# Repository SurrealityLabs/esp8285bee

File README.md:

# esp8285bee
ESP8285 board in an XBee-compatible format

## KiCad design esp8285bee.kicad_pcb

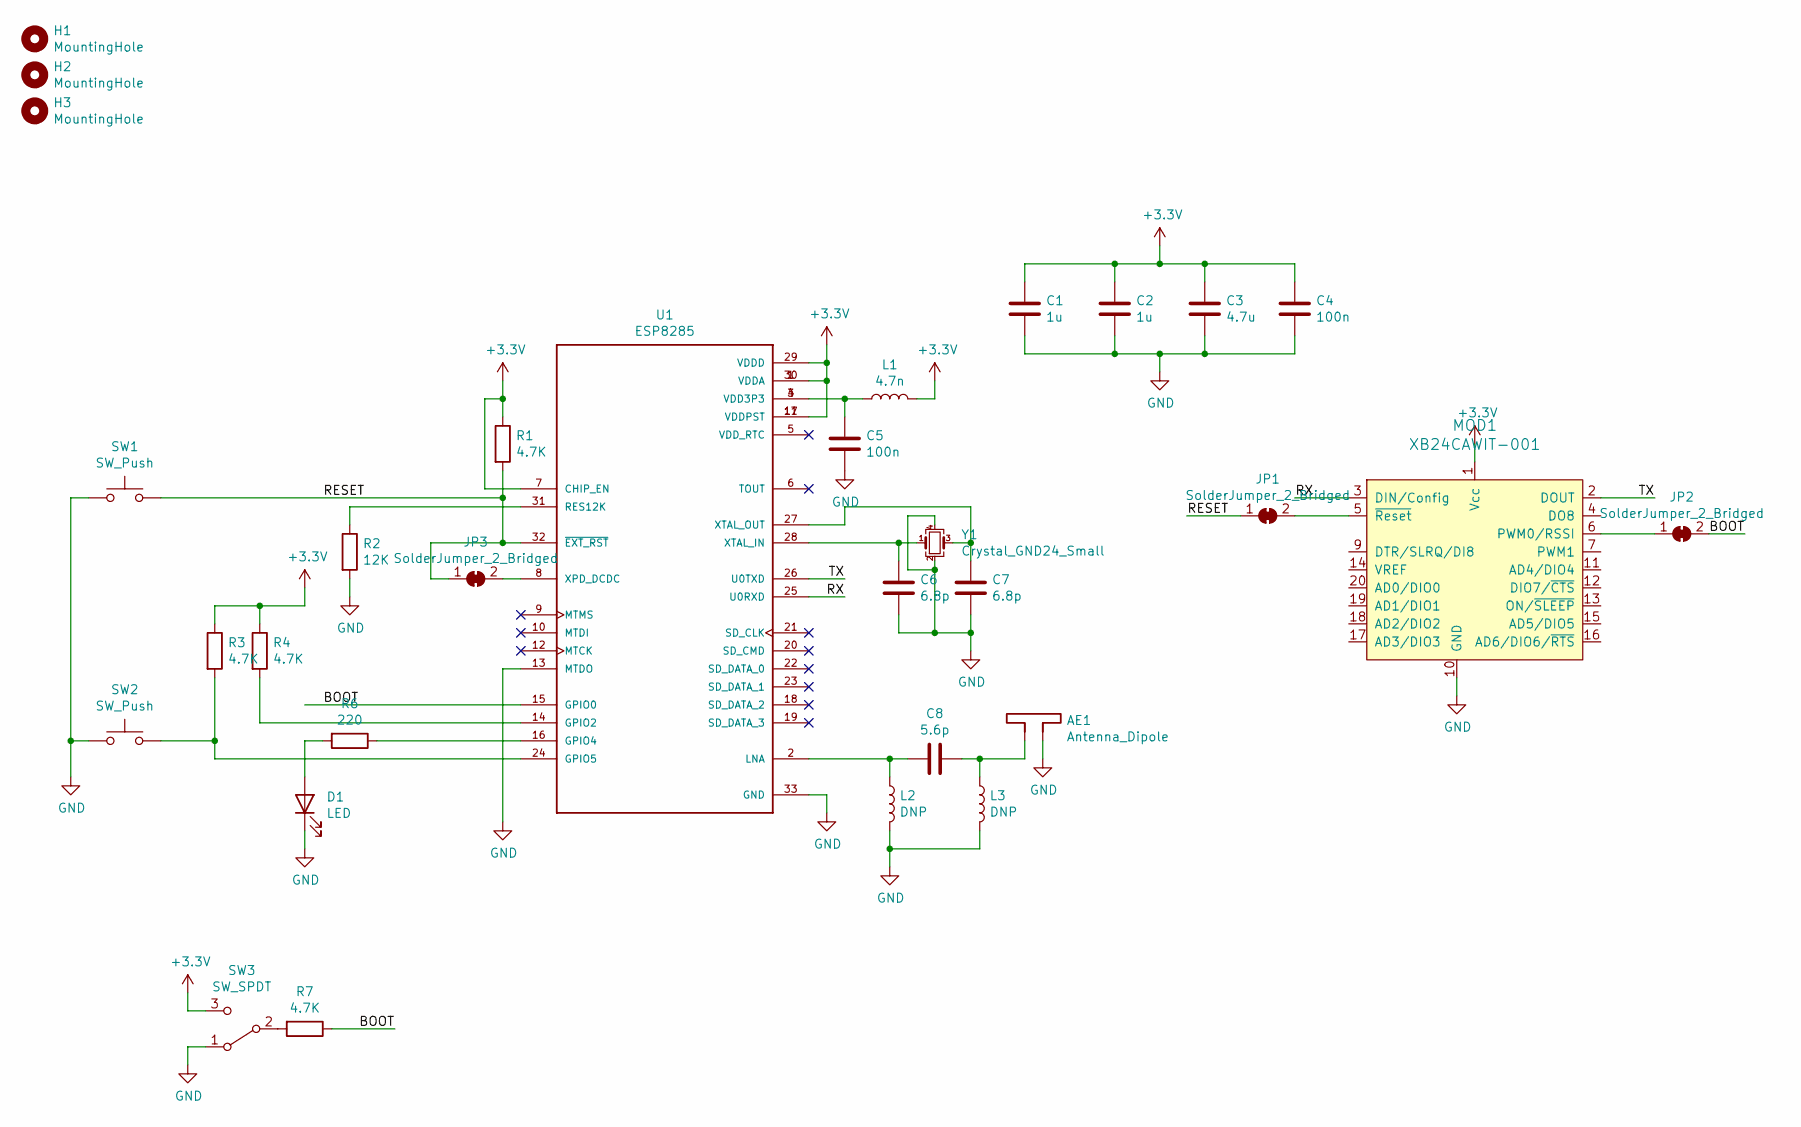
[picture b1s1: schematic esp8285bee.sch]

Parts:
AE1: Antenna_Dipole; Texas_SWRA117D_2.4GHz_Left
C1, C2: 1u; C_0603_1608Metric; LCSC C15849
C3: 4.7u; C_0603_1608Metric; LCSC C19666
C4, C5: 100n; C_0603_1608Metric; LCSC C14663
C6, C7: 6.8p; C_0402_1005Metric; LCSC C1576
C8: 5.6p; C_0402_1005Metric; LCSC C318596
D1: LED; LED_0603; LCSC C72041
H1, H2, H3: MountingHole; tooling-hole
JP1, JP2, JP3: SolderJumper_2_Bridged; SolderJumper-2_P1.3mm_Bridged_RoundedPad1.0x1.5mm
L1: 4.7n; L_0603; LCSC C1030
L2, L3: DNP; L_0402
MOD1: XB24CAWIT-001; XBEE-20_THT; MPN XB24CAWIT-001; Digi-Key_PN 602-1891-ND
R1, R3, R4, R7: 4.7K; R_0603_1608Metric; LCSC C23162
R2: 12K; R_0603_1608Metric; LCSC C22790
R6: 220; R_0603_1608Metric; LCSC C22962
SW1, SW2: SW_Push; SW_SPST_TL3342; LCSC C318888
SW3: SW_SPDT; SW_SPDT_PCM12
U1: ESP8285; QFN-32-1EP_5x5mm_Pitch0.5mm; LCSC C83901
Y1: Crystal_GND24_Small; Crystal_SMD_3225-4Pin_3.2x2.5mm; LCSC C23425

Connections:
+3V3: C1.1, C2.1, C3.1, C4.1, L1.2, MOD1.1 (Vcc), R1.1, R3.1, R4.1, SW3.3 (C), U1.1 (VDDA), U1.7 (CHIP_EN), U1.11 (VDDPST), U1.17 (VDDPST), U1.29 (VDDD), U1.30 (VDDA)
/BOOT: JP2.2 (B), R7.1, U1.15 (GPIO0)
/RESET: JP1.1 (A), JP3.1 (A), R1.2, SW1.2, U1.32 (~EXT_RST~)
/RX: MOD1.3 (DIN/Config), U1.25 (U0RXD)
/TX: MOD1.2 (DOUT), U1.26 (U0TXD)
GND: AE1.2, C1.2, C2.2, C3.2, C4.2, C5.2, C6.2, C7.2, D1.1 (K), L2.2, L3.2, MOD1.10 (GND), R2.2, SW1.1, SW2.1, SW3.1 (A), U1.13 (MTDO), U1.33 (GND), Y1.2, Y1.4
unnamed: AE1.1, C8.2, L3.1
unnamed: C5.1, L1.1, U1.3 (VDD3P3), U1.4 (VDD3P3)
unnamed: C6.1, U1.28 (XTAL_IN), Y1.1
unnamed: C7.1, U1.27 (XTAL_OUT), Y1.3
unnamed: C8.1, L2.1, U1.2 (LNA)
unnamed: D1.2 (A), R6.2
unnamed: JP1.2 (B), MOD1.5 (~Reset)
unnamed: JP2.1 (A), MOD1.6 (PWM0/RSSI)
unnamed: JP3.2 (B), U1.8 (XPD_DCDC)
unnamed: R2.1, U1.31 (RES12K)
unnamed: R3.2, SW2.2, U1.24 (GPIO5)
unnamed: R4.2, U1.14 (GPIO2)
unnamed: R6.1, U1.16 (GPIO4)
unnamed: R7.2, SW3.2 (B)

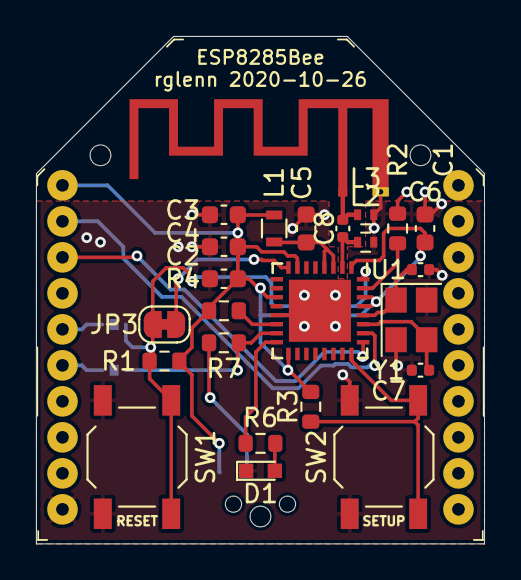
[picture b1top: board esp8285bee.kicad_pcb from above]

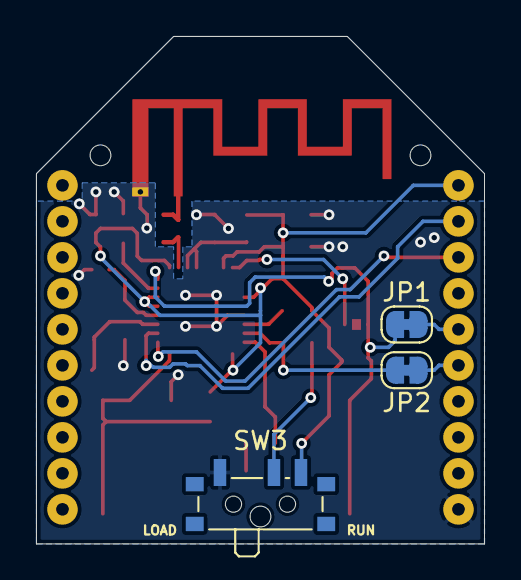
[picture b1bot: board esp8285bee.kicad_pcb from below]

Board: 2 copper layers, 24.9 x 28.2 mm, 31 parts (3 on the bottom side), 20 nets.

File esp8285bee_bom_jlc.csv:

"Comment","Designator","Footprint","LCSC Part #"
"1u","C1,C2","C_0603_1608Metric","C15849"
"4.7u","C3","C_0603_1608Metric","C19666"
"100n","C4,C5","C_0603_1608Metric","C14663"
"6.8p","C7,C6","C_0402_1005Metric","C1576"
"5.6p","C8","C_0402_1005Metric","C318596"
"LED","D1","LED_0603","C72041"
"4.7n","L1","L_0603","C1030"
"4.7K","R1,R4,R3,R7","R_0603_1608Metric","C23162"
"12K","R2","R_0603_1608Metric","C22790"
"220","R6","R_0603_1608Metric","C22962"
"SW_Push","SW2,SW1","SW_SPST_TL3342","C318888"
"ESP8285","U1","QFN-32-1EP_5x5mm_Pitch0.5mm","C83901"
"Crystal_GND24_Small","Y1","Crystal_SMD_3225-4Pin_3.2x2.5mm","C23425"

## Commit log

2021-01-16 Adding PCB as built
2021-01-16 Adding JLCPCB BOM and CPL files
